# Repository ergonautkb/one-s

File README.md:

# Ergonaut One S

*Ergonaut One S in Modern Case*

Ergonaut One S is an open-source ergonomic wireless split mechanical keyboard designed by Ergonaut Keyboards.

Inspiration for the keyboard was taken from these projects:

- [Ergonaut One](https://ergonautkb.com/docs/keyboards/ergonaut-one/intro/) by [Ergonaut Keyboards](https://ergonautkb.com/)
- [Chocofi](https://github.com/pashutk/chocofi/) by [pashutk](https://github.com/pashutk/)

## Idea

We wanted to create a pretty affordable, nice looking, and, most importantly, very DIY-friendly ergonomic wireless split keyboard with Gateron Low Profile switches.

## Features

* Low-profile, which will reduce strain on your beautiful hands;
* Split. You can put the keyboard where it'll be comfortable exactly for you;
* Pretty long battery life. 250mAh battery gives up to a month of usage without charging;
* Wide availability and range of [compatible keycaps](https://ergonautkb.com/docs/switches/gateron-low-profile#keycaps-compatibility);
* Budget-friendly, because:
  * It uses relatively cheap and widely available [Seeed Studio XIAO nRF52840](https://wiki.seeedstudio.com/XIAO_BLE/) as MCU;
  * It uses one PCB design for both halves of the keyboard;
  * Everything except PCB's, components and hardware (screws, nuts) can be 3D printed.
* Beginner-friendly, because:
  * PCB is easy to solder;
  * Cases are easy to print.
* Wireless by design - no unnecessary wires, no unused connectors on the board;
* Free in terms of hardware design. It's licensed under permissive [CERN-OHL-P v2](https://ohwr.org/cern_ohl_p_v2.pdf) license, which means:
  * you are free to manufacture it yourself;
  * you are free to sell your manufactured hardware for profit.

## Build Guide

BOM and Build Guide can be found in [Ergonaut Keyboards Documentation Portal](https://ergonautkb.com/docs/keyboards/ergonaut-one-s/intro).

## Firmware

Firmware can be found in [one-zmk-config](https://github.com/ergonautkb/one-s-zmk-config) repository.

## Gerbers

| Front                                            | Back                                                 |
| ------------------------------------------------ | ---------------------------------------------------- |
|  |  |

* [JLCPCB](../../releases/latest/download/pcb-JLCPCB_gerbers.zip)
* [PCBWay](../../releases/latest/download/pcb-PCBWay_gerbers.zip)

## Contacts

* Documentation portal: https://ergonautkb.com
* Telegram: https://ergonautkb.t.me
* Telegram (ru): https://ergonautkb_ru.t.me

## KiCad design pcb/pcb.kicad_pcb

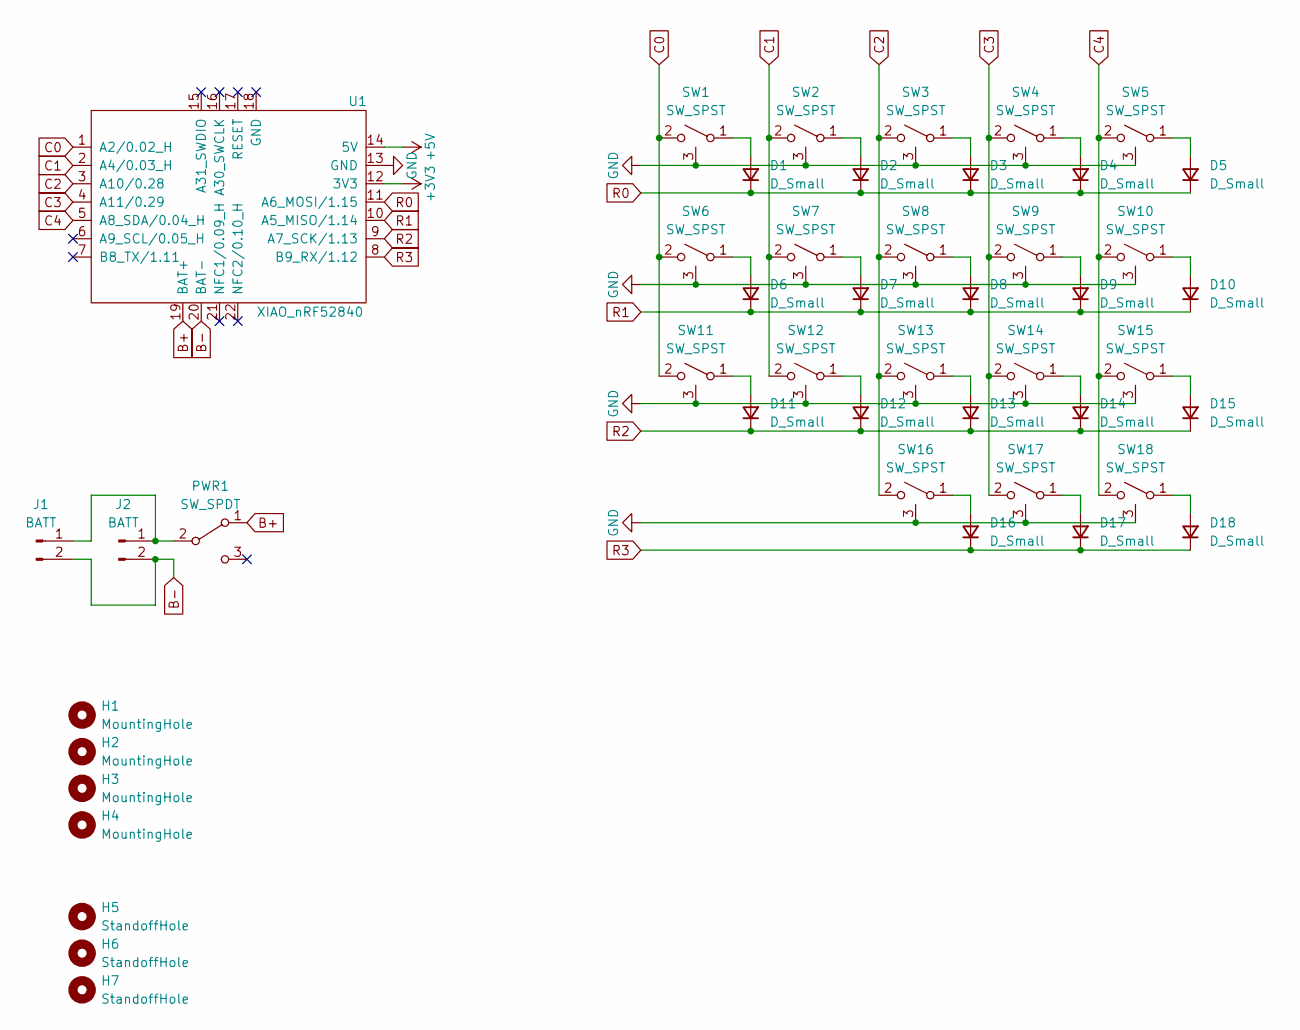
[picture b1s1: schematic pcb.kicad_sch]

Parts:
D1, D2, D3, D4, D5, D6, D7, D8, D9, D10, D11, D12, D13, D14, D15, D16, D17, D18: D_Small; Diode_TH_SMD_DUAL
H1, H2, H3, H4: MountingHole; Hole_4.2mm
H5, H6, H7: StandoffHole; Hole_2.2mm
J1: BATT; JST_SH_Battery_DUAL
J2: BATT; Battery
PWR1: SW_SPDT; MSK-12C02_DUAL
SW1, SW2, SW3, SW4, SW5, SW6, SW7, SW8, SW9, SW10, SW11, SW12, SW13, SW14, SW15, SW16, SW17, SW18: SW_SPST; CPG1316S01D02_REV
U1: XIAO_nRF52840; XIAO_nRF52840_DUAL

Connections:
+3V3: U1.12 (3V3)
+5V: U1.14 (5V)
B+: PWR1.1 (A), U1.19 (BAT+)
B-: J1.2, J2.2, U1.20 (BAT-)
C0: SW1.2 (B), SW6.2 (B), SW11.2 (B), U1.1 (A2/0.02_H)
C1: SW2.2 (B), SW7.2 (B), SW12.2 (B), U1.2 (A4/0.03_H)
C2: SW3.2 (B), SW8.2 (B), SW13.2 (B), SW16.2 (B), U1.3 (A10/0.28)
C3: SW4.2 (B), SW9.2 (B), SW14.2 (B), SW17.2 (B), U1.4 (A11/0.29)
C4: SW5.2 (B), SW10.2 (B), SW15.2 (B), SW18.2 (B), U1.5 (A8_SDA/0.04_H)
GND: SW1.3 (B), SW2.3 (B), SW3.3 (B), SW4.3 (B), SW5.3 (B), SW6.3 (B), SW7.3 (B), SW8.3 (B), SW9.3 (B), SW10.3 (B), SW11.3 (B), SW12.3 (B), SW13.3 (B), SW14.3 (B), SW15.3 (B), SW16.3 (B), SW17.3 (B), SW18.3 (B), U1.13 (GND)
unnamed: D1.2 (A), SW1.1 (A)
unnamed: D2.2 (A), SW2.1 (A)
unnamed: D3.2 (A), SW3.1 (A)
unnamed: D4.2 (A), SW4.1 (A)
unnamed: D5.2 (A), SW5.1 (A)
unnamed: D6.2 (A), SW6.1 (A)
unnamed: D7.2 (A), SW7.1 (A)
unnamed: D8.2 (A), SW8.1 (A)
unnamed: D9.2 (A), SW9.1 (A)
unnamed: D10.2 (A), SW10.1 (A)
unnamed: D11.2 (A), SW11.1 (A)
unnamed: D12.2 (A), SW12.1 (A)
unnamed: D13.2 (A), SW13.1 (A)
unnamed: D14.2 (A), SW14.1 (A)
unnamed: D15.2 (A), SW15.1 (A)
unnamed: D16.2 (A), SW16.1 (A)
unnamed: D17.2 (A), SW17.1 (A)
unnamed: D18.2 (A), SW18.1 (A)
unnamed: J1.1, J2.1, PWR1.2 (B)
R0: D1.1 (K), D2.1 (K), D3.1 (K), D4.1 (K), D5.1 (K), U1.11 (A6_MOSI/1.15)
R1: D6.1 (K), D7.1 (K), D8.1 (K), D9.1 (K), D10.1 (K), U1.10 (A5_MISO/1.14)
R2: D11.1 (K), D12.1 (K), D13.1 (K), D14.1 (K), D15.1 (K), U1.9 (A7_SCK/1.13)
R3: D16.1 (K), D17.1 (K), D18.1 (K), U1.8 (B9_RX/1.12)

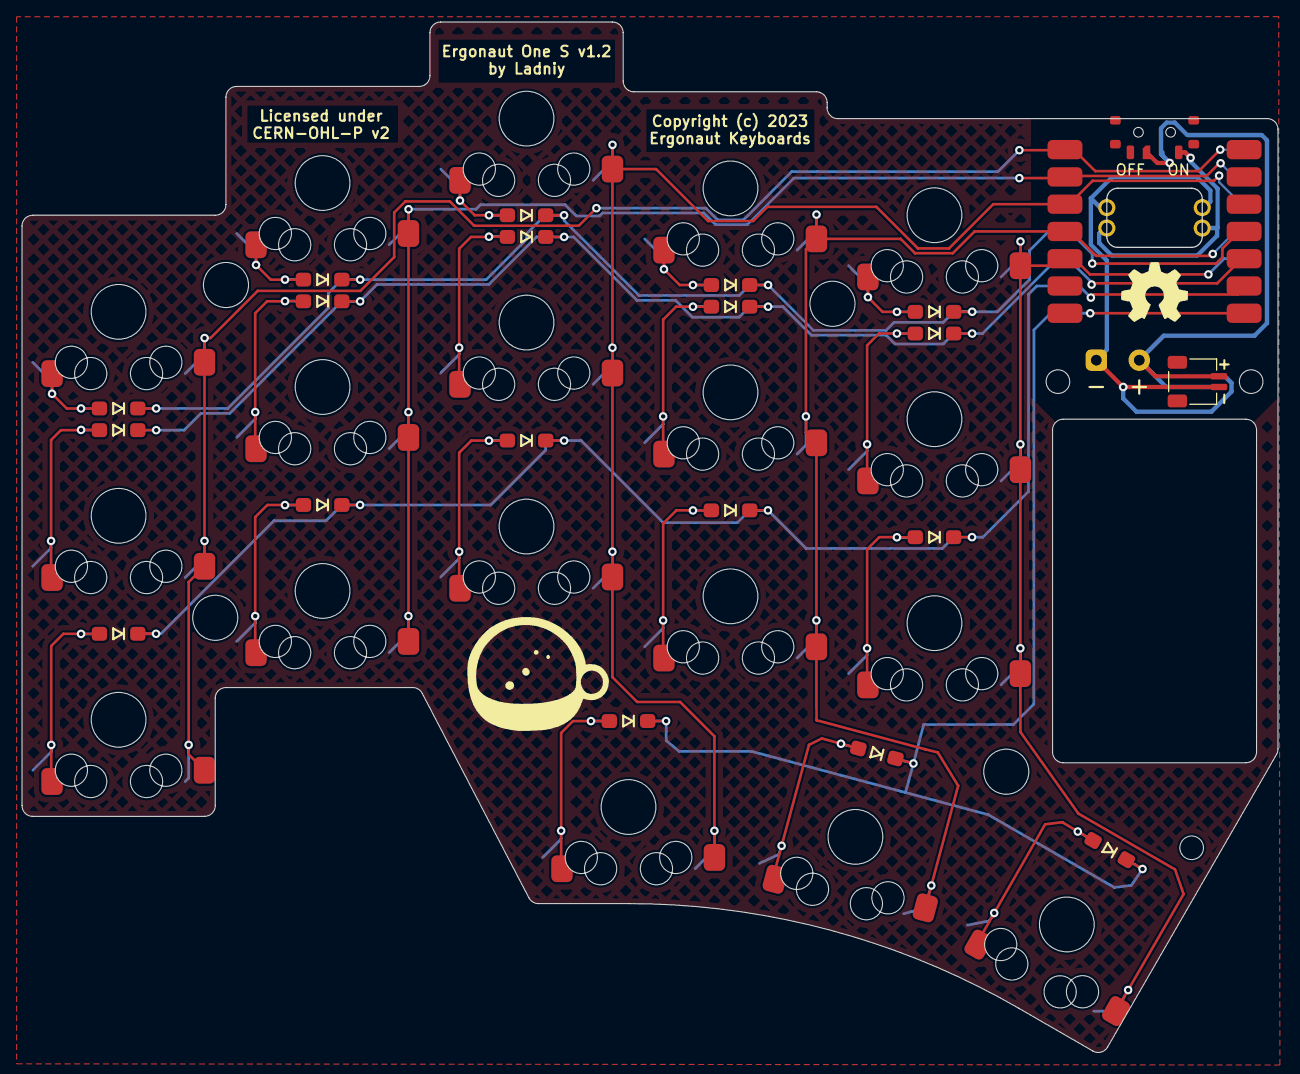
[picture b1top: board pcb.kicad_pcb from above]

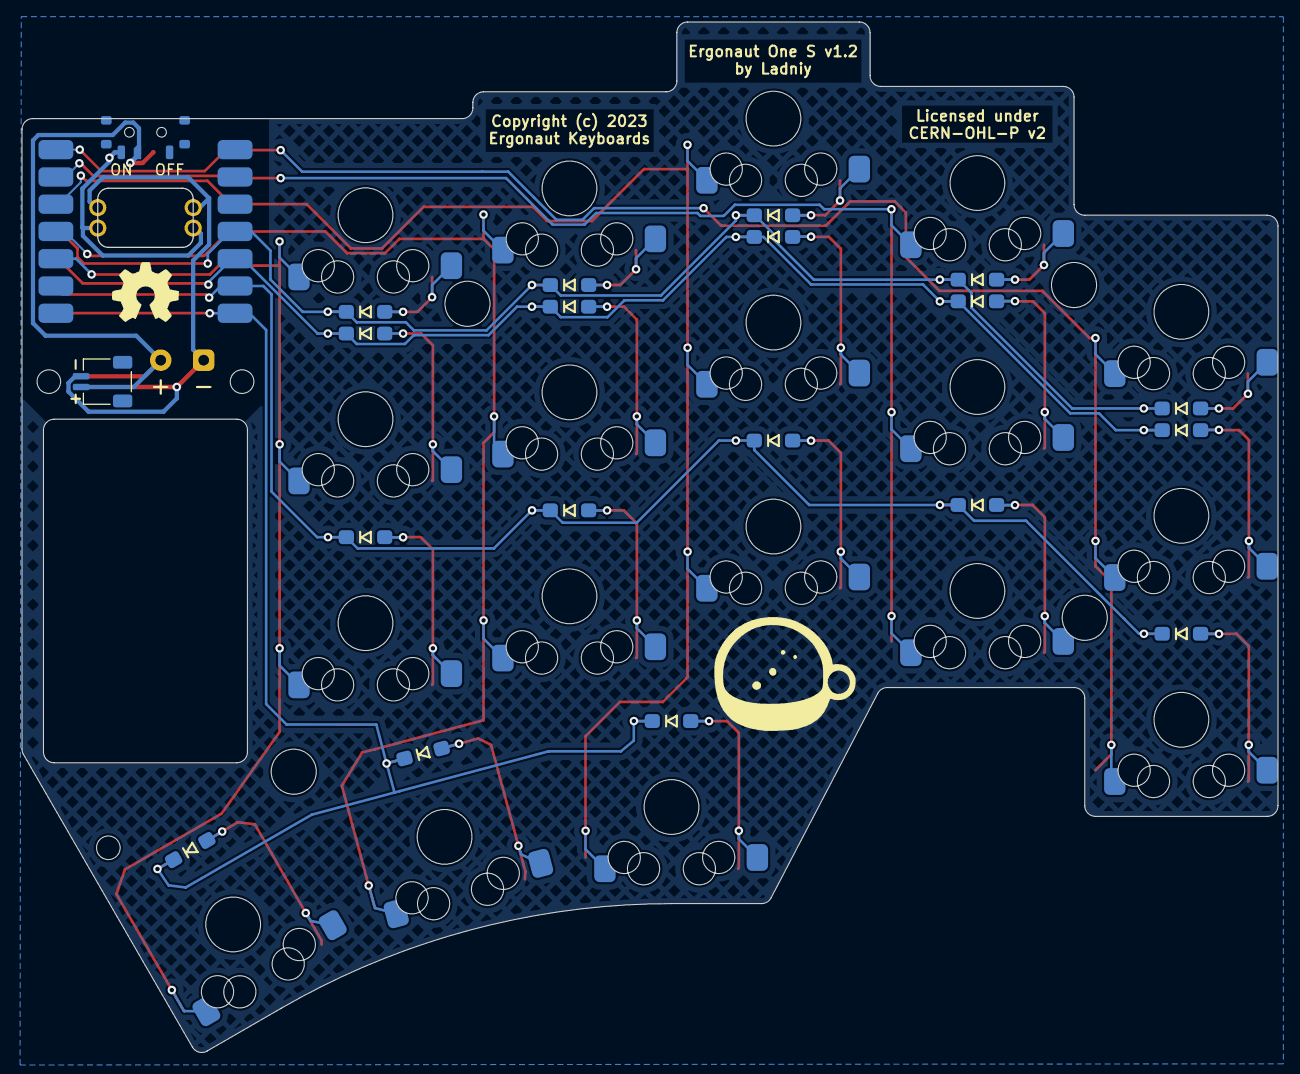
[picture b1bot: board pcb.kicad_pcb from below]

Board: 2 copper layers, 117.0 x 96.0 mm, 47 parts (19 on the bottom side), 30 nets.

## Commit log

2023-07-31 feat: add git ignore file
2023-07-31 feat: add basic drawing
2023-07-31 feat: add libs for kicad
2023-07-31 feat: pcb scheme is ready
2023-07-31 fix: symbol references
2023-08-01 feat: add 3d models
2023-08-01 feat: place all components on pcb
2023-08-01 fix: silkscreen
2023-08-09 fix: diode placement
2023-09-03 feat: everything ready (no way)
2023-12-07 feat: a lot of things, more in future pr
2023-12-07 feat: add keepout zone around mcu
2023-12-11 feat: change fillets radius on battery cutout and move keepout zones a bit
2023-12-11 add ci and 3d files
2023-12-11 fix ci
2024-01-15 Add photo
2024-01-15 Update photo
2024-02-25 Round and enlarge xiao pads, add cutout under controller
2024-02-29 Round and enlarge xiao pads, add cutout under controller (#3)
2024-07-18 Modify PCB for Kailh P1316S
2024-11-24 V1.2: fix missing traces on right half

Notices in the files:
pcb/pcb.kicad_pcb:
Copyright (c) 2023
